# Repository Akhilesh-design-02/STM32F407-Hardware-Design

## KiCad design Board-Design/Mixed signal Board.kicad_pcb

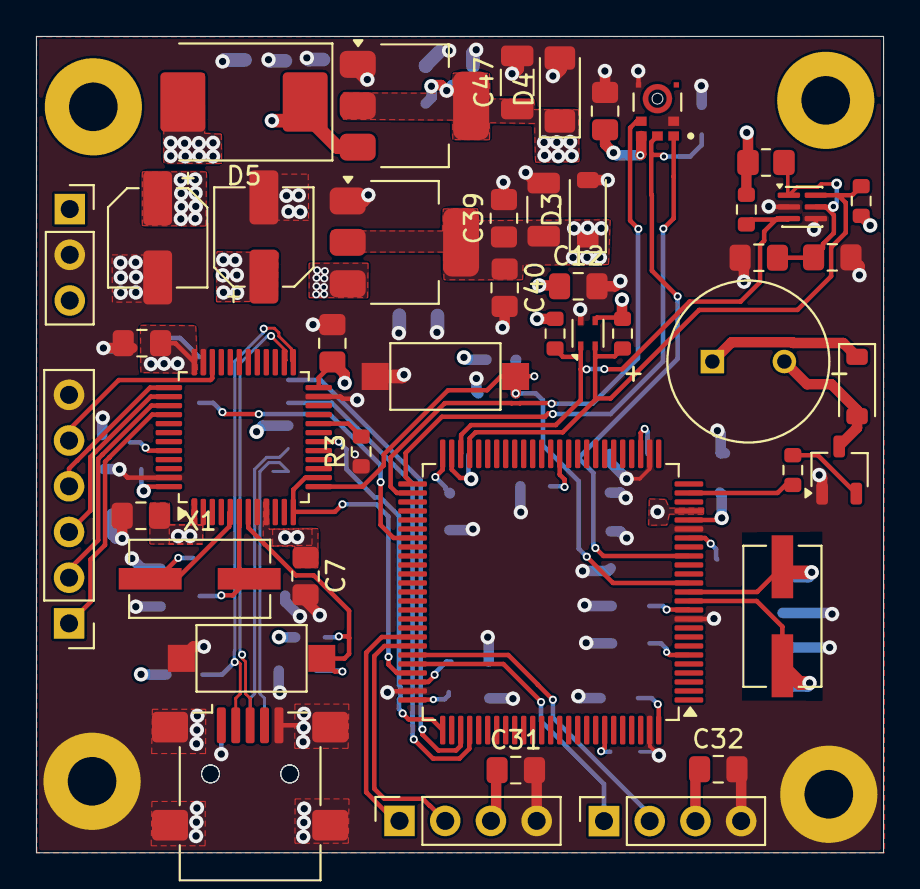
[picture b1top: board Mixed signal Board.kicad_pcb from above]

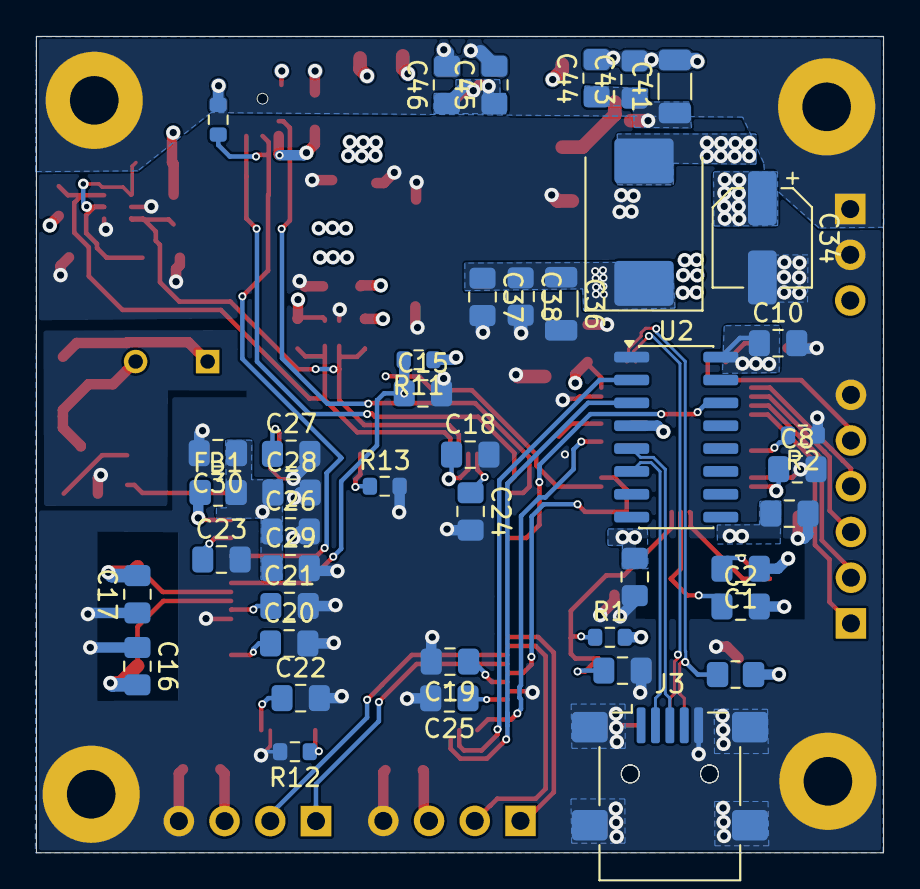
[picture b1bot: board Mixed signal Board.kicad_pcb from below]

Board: 4 copper layers, 47.1 x 45.3 mm, 92 parts (43 on the bottom side), 47 nets.

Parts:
BZ1: CST-931AP; CUI_CST-931AP
C1, C2, C16, C17: 32pF; C_0805_2012Metric_Pad1.18x1.45mm_HandSolder
C3, C4, C5, C6, C7, C10, C11, C12, C15, C20, C21, C22, C23, C24, C25, C26, C28, C31, C32, C38, C39, C44, C45, C48: 0.1uF; C_0805_2012Metric_Pad1.18x1.45mm_HandSolder
C8, C27: 4.7uF; C_0805_2012Metric_Pad1.18x1.45mm_HandSolder
C9, C13, C14, C29, C30, C37, C40, C43, C46: 1uF; C_0805_2012Metric_Pad1.18x1.45mm_HandSolder
C18, C19: 2.2uF; C_0805_2012Metric_Pad1.18x1.45mm_HandSolder
C33, C34, C35: 1uF; CP_Elec_5x5.4
C36, C41, C42, C47: 10uF; C_1206_3216Metric
D1: 1N4148W; D_SOD-123
D2, D5: MBRS130LT3G; D_SMC
D3: BZT52C3V3-7-F; D_SOD-123
D4: ZMM3.3; D_MiniMELF
FB1: 1K; R_0805_2012Metric_Pad1.20x1.40mm_HandSolder
H1, H2, H3, H4: MountingHole_Pad; MountingHole_2.7mm_Pad
J1, J3: USB_B_Mini; USB_Mini-B_Lumberg_2486_01_Horizontal
J2: Conn_01x06; PinHeader_1x06_P2.54mm_Vertical
J4, J5: Conn_01x04; PinSocket_1x04_P2.54mm_Vertical
J6: Terminal Block 2.5mm; PinSocket_1x03_P2.54mm_Vertical
Q1: MMBT3904; TSOT-23
R1, R5, R6, R9, R10, R11: 10KΩ; R_0603_1608Metric
R2, R3: 100Ω; R_0603_1608Metric
R4: 1.5kΩ; R_0805_2012Metric_Pad1.20x1.40mm_HandSolder
R7: 180Ω; R_0603_1608Metric
R8: 4.7Ω; R_0805_2012Metric_Pad1.20x1.40mm_HandSolder
R12, R13, R14: 100KΩ; R_0603_1608Metric
SW1, SW2: TACTILE SWITCH; SW_SPST_CK_RS282G05A3
U1: STM32F103C8Tx; LQFP-48_7x7mm_P0.5mm
U2: CH340C; SOIC-16_3.9x9.9mm_P1.27mm
U3: MMICT5848-00-012; MIC_MMICT5848-00-012
U4: SHT40-AD1B-R2; Sensirion_DFN-4_1.5x1.5mm_P0.8mm_SHT4x_NoCentralPad
U5: SGP40-D-R4; Broadcom_DFN-6_2x2mm_P0.65mm
U6: STM32F407VGTx; LQFP-100_14x14mm_P0.5mm
U7: LD1117S33TR_SOT223; SOT-223-3_TabPin2
U8: LD1117S18TR_SOT223; SOT-223-3_TabPin2
X1, X2: 8MHZ; Crystal_SMD_ECS_CSM3X-2Pin_7.6x4.1mm

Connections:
+1V8: C11.1, C45.1, C46.1, C47.1, D4.1 (K), U3.7 (VDD), U8.2 (VO)
+3V3: BZ1.P, C3.1, C4.1, C5.1, C6.1, C7.1, C8.1, C9.1, C10.1, C12.1, C20.1, C21.1, C22.1, C23.1, C24.1, C25.1, C27.1, C31.1, C32.1, C39.1, C40.1, C42.1, D1.1 (K), D3.1 (K), FB1.1, J4.3, J5.3, R1.2, R4.1, R5.1, R6.1, R8.1, R9.1, R10.1, R11.1, U1.1 (VBAT), U1.9 (VDDA), U1.24 (VDD), U1.36 (VDD), U1.48 (VDD), U2.4 (V3), U2.16 (VCC), U4.3 (VDD), U6.6 (VBAT), U6.11 (VDD), U6.19 (VDD), U6.21 (VREF+), U6.28 (VDD), U6.50 (VDD), U6.75 (VDD), U6.100 (VDD), U7.2 (VO)
+5V1: C33.1, C34.1, C35.1, D2.2 (A), D5.2 (A), J6.3
/[3]-STM32F103 Debugger Sch./JTCK/SWCLK_F103: J2.4, U1.37 (PA14)
/[3]-STM32F103 Debugger Sch./JTD0_F103: J2.2, U1.39 (PB3)
/[3]-STM32F103 Debugger Sch./JTDI_F103: J2.3, U1.38 (PA15)
/[3]-STM32F103 Debugger Sch./JTMS/SWD_F103: J2.5, U1.34 (PA13)
/[3]-STM32F103 Debugger Sch./NRST: C48.1, R1.1, SW1.2 (D), U1.7 (NRST)
/[3]-STM32F103 Debugger Sch./NTJRST_F103: J2.1, U1.40 (PB4)
/[3]-STM32F103 Debugger Sch./USBD_N: J1.3 (D+), U1.26 (PB13)
/[3]-STM32F103 Debugger Sch./USBD_P: J1.2 (D-), R4.2, U1.25 (PB12)
/[4]- CH340C/CH340USB_N: J3.2 (D-), U2.6 (UD-)
/[4]- CH340C/CH340USB_P: J3.3 (D+), U2.5 (UD+)
/[6]-STM32F407 Main controller/CAN_RX: J5.1, U6.71 (PA12)
/[6]-STM32F407 Main controller/CAN_TX: J5.2, U6.70 (PA11)
/[6]-STM32F407 Main controller/EXT UART_RX: J4.2, U6.69 (PA10)
/[6]-STM32F407 Main controller/EXT UART_TX: J4.1, U6.68 (PA9)
Buzzer_I/P: R7.1, U6.24 (PA1)
CH340_RST: U2.14 (~RTS), U6.57 (PD10)
CH340_RXD: U2.3 (RXD), U6.79 (PC11)
CH340_TXD: U2.2 (TXD), U6.78 (PC10)
Earth: H1.1 (1_1), H3.1 (1_1), J6.1
GND: C1.1, C2.2, C3.2, C4.2, C5.2, C6.2, C7.2, C8.2, C9.2, C10.2, C11.2, C12.2, C13.2, C14.2, C15.2, C16.1, C17.1, C18.2, C19.2, C20.2, C21.2, C22.2, C23.2, C24.2, C25.2, C26.2, C27.2, C28.2, C29.2, C30.2, C31.2, C32.2, C33.2, C34.2, C35.2, C36.2, C37.2, C38.2, C39.2, C40.2, C41.2, C42.2, C43.2, C44.2, C45.2, C46.2, C47.2, C48.2, D3.2 (A), D4.2 (A), H2.1 (1_1), H4.1 (1_1), J1.5 (GND), J1.SH (Shield), J2.6, J3.5 (GND), J3.SH (Shield), J4.4, J5.4, J6.2, Q1.1 (E1), R2.1, R3.1, R12.2, R13.2, R14.2, SW1.1 (C), SW2.1 (C), U1.8 (VSSA), U1.23 (VSS), U1.35 (VSS), U1.47 (VSS), U2.1 (GND), U3.2 (LR), U3.5 (THSEL), U4.4 (VSS), U5.2 (VSS), U5.4 (n/a), U6.10 (VSS), U6.20 (VSSA), U6.27 (VSS), U6.74 (VSS), U6.99 (VSS), U7.1 (GND), U8.1 (GND)
I2C_SCL: R5.2, R10.2, U4.2 (SCL), U5.6 (SCL), U6.47 (PB10)
I2C_SDA: R6.2, R9.2, U4.1 (SDA), U5.3 (SDA), U6.48 (PB11)
I2S_SCL: U3.6 (SCLK), U6.52 (PB13)
I2S_WS: U3.1 (WS), U6.51 (PB12)
JTCLK_407: U1.18 (PB0), U6.76 (PA14)
JTMS_F407: U1.12 (PA2), U1.14 (PA4), U6.72 (PA13)
MMIC_SD: R14.1, U3.8 (SD), U6.17 (PC2)
NTRST_F407: C15.1, R11.2, SW2.2 (D), U1.13 (PA3), U6.14 (NRST)
unnamed: BZ1.M, D1.2 (A), Q1.3 (C1)
unnamed: C36.1, C37.1, C38.1, D2.1 (K), U7.3 (VI)
unnamed: C41.1, C43.1, C44.1, D5.1 (K), U8.3 (VI)
unnamed: Q1.2 (B1), R7.2
unnamed: R2.2, U1.44 (BOOT0)
unnamed: R3.2, U1.20 (PB2)
unnamed: C1.2, U1.5 (PD0), X1.1
unnamed: C2.1, U1.6 (PD1), X1.2
unnamed: C13.1, C14.1, R8.2, U5.1 (VDD), U5.5 (VDDH)
unnamed: R12.1, U6.94 (BOOT0)
unnamed: R13.1, U6.37 (PB2)
unnamed: C16.2, U6.12 (PH0), X2.2
unnamed: C17.2, U6.13 (PH1), X2.1
unnamed: C18.1, U6.49 (VCAP_1)
unnamed: C19.1, U6.73 (VCAP_2)
unnamed: C26.1, C28.1, C29.1, C30.1, FB1.2, U6.22 (VDDA)
